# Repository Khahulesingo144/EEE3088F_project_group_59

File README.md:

# EEE3088F 2025 Micro-Mouse Power Subsystem

## Overview
This repository contains all design files and documentation for the power subsystem of the Micro-Mouse project, as part of the EEE3088F 2025 course at the University of Cape Town. 

The power module is responsible for delivering regulated power to the entire micro-mouse system, supporting motor driving, USB-C power input, battery monitoring and charging, and high-side switching for external loads.

## Project Objectives
- Design and manufacture a power PCB that:
  - Powers 4 motors (2x 200mA and 2x 500mA brushed DC)
  - Charges a LiPo battery from a 9V USB-C input (with 200mA and ~600mA charge modes)
  - Integrates an INA219 sensor for battery voltage/current monitoring
  - Supplies 5V @ 1.5A and 3.3V @ 300mA regulated outputs
  - Supports dual high-side external load switching (1A each)
  - Includes ON/OFF switching (<30μA off-state draw, 2A on-state peak)
- Stay within the strict $70 budget for manufacturing and components
- Ensure physical compatibility with the provided micro-mouse motherboard

## Tools Used
- **KiCad** – Schematic capture and PCB layout
- **JLCPCB** – PCB manufacturing and assembly
- **Git** – Version control
- **LaTeX** – Report writing

## Key Files
- `jlcpcb/production_files/GERBER-EEE3088F_2025_Project.zip` – Final Gerber files for PCB manufacturing
- `jlcpcb/production_files/BOM-EEE3088F_2025_Project.csv` – Bill of Materials for JLCPCB
- `jlcpcb/production_files/CPL-EEE3088F_2025_Project.csv` – Pick and Place file for assembly

## Contributors
- **Student 1**: Khahule Singo, Student Number: SNGKHA008
- **Student 2**: Otsile Diale, Student Number: DLXOTS001

Each student is responsible for distinct sections of the design and has submitted an individual report accordingly.

## License
This repository is intended for academic use only. Please do not reproduce or redistribute without permission.

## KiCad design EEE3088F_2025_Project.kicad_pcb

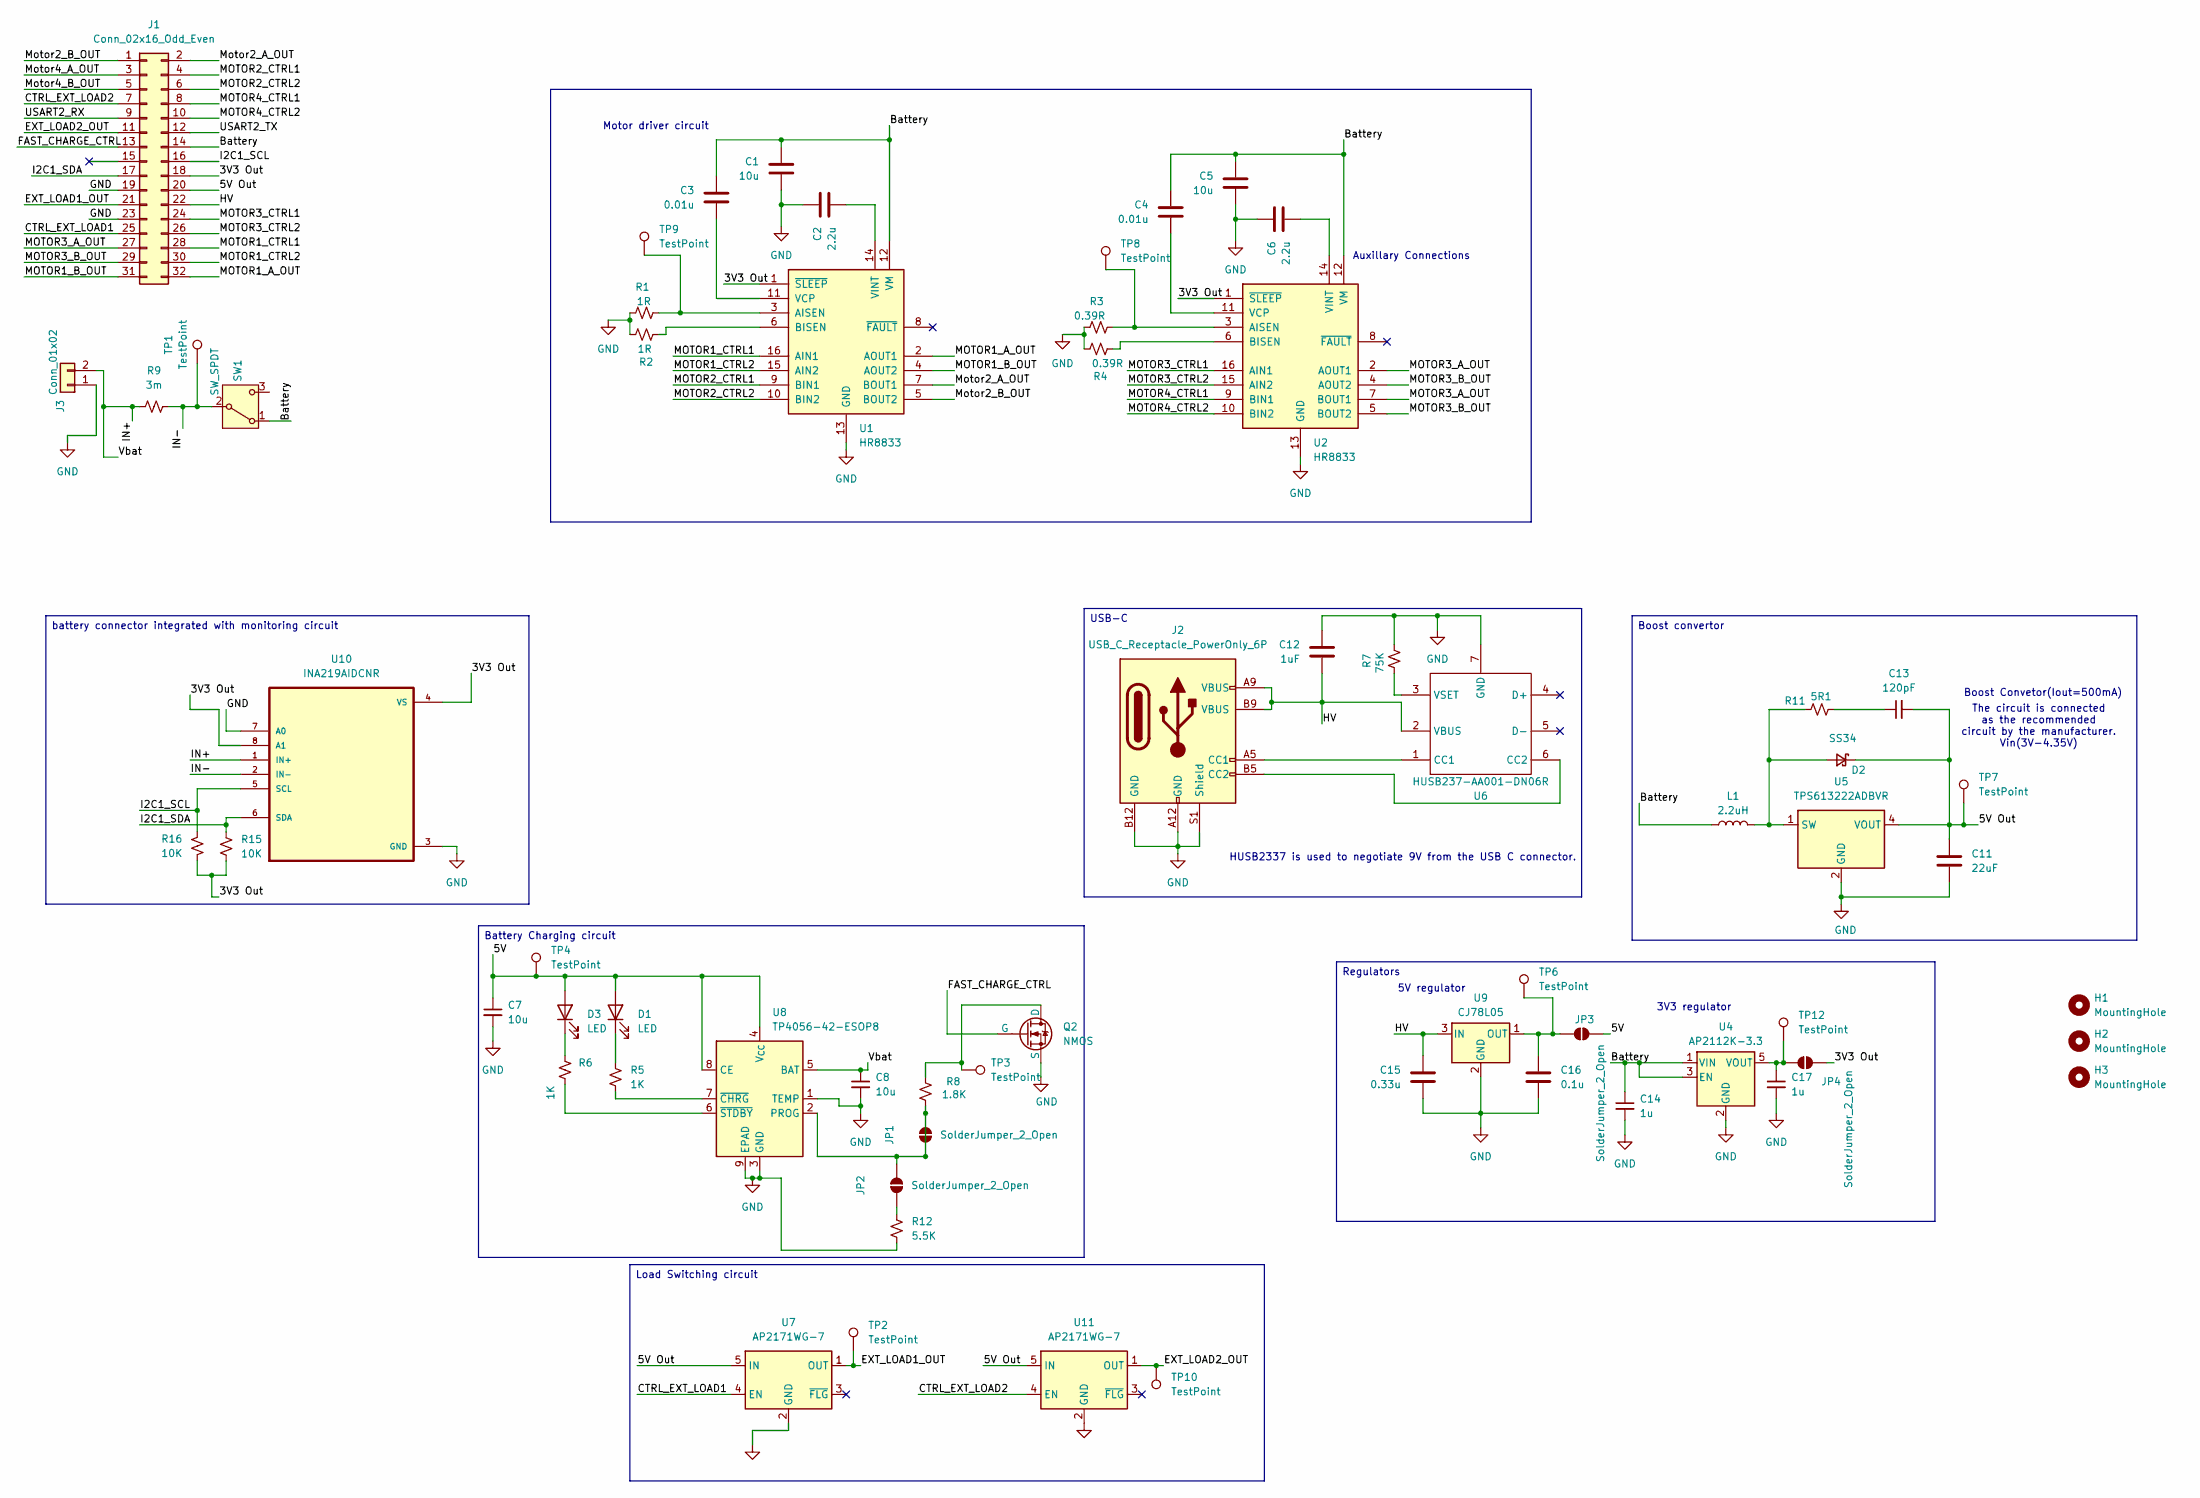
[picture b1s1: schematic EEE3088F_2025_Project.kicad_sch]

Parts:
C1, C5, C7, C8: 10u; C_0805_2012Metric_Pad1.18x1.45mm_HandSolder
C2, C6: 2.2u; C_0805_2012Metric_Pad1.18x1.45mm_HandSolder; LCSC C377773
C3, C4: 0.01u; C_0805_2012Metric_Pad1.18x1.45mm_HandSolder; LCSC C1710
C11: 22uF; C_0805_2012Metric_Pad1.18x1.45mm_HandSolder
C12: 1uF; C_0805_2012Metric_Pad1.18x1.45mm_HandSolder
C13: 120pF; C_0805_2012Metric_Pad1.18x1.45mm_HandSolder; LCSC C18438
C14: 1u; C_0805_2012Metric_Pad1.18x1.45mm_HandSolder
C15: 0.33u; C_0201_0603Metric_Pad0.64x0.40mm_HandSolder; LCSC C5139492
C16: 0.1u; C_0201_0603Metric_Pad0.64x0.40mm_HandSolder; LCSC C1525
C17: 1u; C_0805_2012Metric_Pad1.18x1.45mm_HandSolder; LCSC C28323
D1, D3: LED; LED_0201_0603Metric_Pad0.64x0.40mm_HandSolder
D2: SS34; D_SMA; LCSC C8678
H1, H2, H3: MountingHole; MountingHole_3.2mm_M3_DIN965_Pad
J1: Conn_02x16_Odd_Even; PinHeader_2x16_P2.54mm_Vertical
J2: USB_C_Receptacle_PowerOnly_6P; USB_C_Receptacle_GCT_USB4125-xx-x_6P_TopMnt_Horizontal; LCSC C456012
J3: Conn_01x02; JST_PH_S2B-PH-K_1x02_P2.00mm_Horizontal; LCSC C541760
JP1, JP2, JP3, JP4: SolderJumper_2_Open; SolderJumper-2_P1.3mm_Open_Pad1.0x1.5mm
L1: 2.2uH; L_1008_2520Metric_Pad1.43x2.20mm_HandSolder; LCSC C86092
Q2: NMOS; SOT-23-3; LCSC C20917
R1, R2: 1R; R1206; LCSC C17928
R3, R4: 0.39R; R1206; LCSC C188072
R5, R6: 1K; R_0201_0603Metric_Pad0.64x0.40mm_HandSolder
R7: 75K; R_0603_1608Metric_Pad0.98x0.95mm_HandSolder; LCSC C23242
R8: 1.8K; R_0201_0603Metric_Pad0.64x0.40mm_HandSolder; LCSC C4177
R9: 3m; R2512; LCSC C5375459
R11: 5R1; R_0805_2012Metric_Pad1.20x1.40mm_HandSolder; LCSC C17724
R12: 5.5K; R_0201_0603Metric_Pad0.64x0.40mm_HandSolder; LCSC C4382
R15, R16: 10K; R1206
SW1: SW_SPDT; SW_Slide_SPDT_Angled_CK_OS102011MA1Q; LCSC C431548
TP1, TP2, TP3, TP4, TP6, TP7, TP8, TP9, TP10, TP12: TestPoint; TestPoint_THTPad_D2.0mm_Drill1.0mm
U1, U2: HR8833; TSSOP-16_4.4x5mm_P0.65mm; LCSC C128666
U4: AP2112K-3.3; SOT-25-5_L2.9-W1.6-P0.95-LS2.8-BL; LCSC C51118
U5: TPS613222ADBVR; SOT-23-5; LCSC C2071163
U6: HUSB237-AA001-DN06R; DFN-6-1EP_2x2mm_P0.65mm_EP1.01x1.7mm; LCSC C22373734
U7, U11: AP2171WG-7; SOT-25-5_L2.9-W1.6-P0.95-LS2.8-BL; LCSC C110466
U8: TP4056-42-ESOP8; SOIC-8-1EP_3.9x4.9mm_P1.27mm_EP2.41x3.3mm_ThermalVias; LCSC C16581
U9: CJ78L05; SOT-89-3; LCSC C2079
U10: INA219AIDCNR; SOT-23-8_Handsoldering; LCSC C87469

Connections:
/3V3 Out: J1.18, JP4.1 (A), R15.2, R16.2, U1.1 (~SLEEP), U2.1 (~SLEEP), U10.4 (VS), U10.8 (A1)
/5V: C7.1, D1.2 (A), D3.2 (A), JP3.1 (A), TP4.1, U8.4 (V_{CC}), U8.8 (CE)
/5V Out: C11.1, C13.2, D2.1 (K), J1.20, TP7.1, U5.4 (VOUT), U7.5 (IN), U11.5 (IN)
/Battery: C1.1, C3.1, C4.1, C5.1, C14.1, J1.14, L1.1, SW1.1 (A), U1.12 (VM), U2.12 (VM), U4.1 (VIN), U4.3 (EN)
/CTRL_EXT_LOAD1: J1.25, U7.4 (EN)
/CTRL_EXT_LOAD2: J1.7, U11.4 (EN)
/EXT_LOAD1_OUT: J1.21, TP2.1, U7.1 (OUT)
/EXT_LOAD2_OUT: J1.11, TP10.1, U11.1 (OUT)
/FAST_CHARGE_CTRL: J1.13, Q2.2 (G)
/HV: C12.2, C15.1, J1.22, J2.A9 (VBUS), J2.B9 (VBUS), U6.2 (VBUS), U9.3 (IN)
/I2C1_SCL: J1.16, R16.1, U10.5 (SCL)
/I2C1_SDA: J1.17, R15.1, U10.6 (SDA)
/IN+: C8.1, J3.2, R9.1, U8.5 (BAT), U10.1 (IN+)
/IN-: R9.2, SW1.2 (B), TP1.1, U10.2 (IN-)
/MOTOR1_A_OUT: J1.32, U1.2 (AOUT1)
/MOTOR1_B_OUT: J1.31, U1.4 (AOUT2)
/MOTOR1_CTRL1: J1.28, U1.16 (AIN1)
/MOTOR1_CTRL2: J1.30, U1.15 (AIN2)
/MOTOR2_CTRL1: J1.4, U1.9 (BIN1)
/MOTOR2_CTRL2: J1.6, U1.10 (BIN2)
/MOTOR3_A_OUT: J1.27, U2.2 (AOUT1), U2.7 (BOUT1)
/MOTOR3_B_OUT: J1.29, U2.4 (AOUT2), U2.5 (BOUT2)
/MOTOR3_CTRL1: J1.24, U2.16 (AIN1)
/MOTOR3_CTRL2: J1.26, U2.15 (AIN2)
/MOTOR4_CTRL1: J1.8, U2.9 (BIN1)
/MOTOR4_CTRL2: J1.10, U2.10 (BIN2)
/Motor2_A_OUT: J1.2, U1.7 (BOUT1)
/Motor2_B_OUT: J1.1, U1.5 (BOUT2)
/Motor4_A_OUT: J1.3
/Motor4_B_OUT: J1.5
/USART2_RX: J1.9
/USART2_TX: J1.12
GND: C1.2, C2.1, C5.2, C6.1, C7.2, C8.2, C11.2, C12.1, C14.2, C15.2, C16.2, C17.2, H1.1, H2.1, H3.1, J1.19, J1.23, J2.A12 (GND), J2.B12 (GND), J2.S1 (Shield), J3.1, Q2.3 (S), R1.1, R2.1, R3.1, R4.1, R7.1, R12.2, U1.13 (GND), U2.13 (GND), U4.2 (GND), U5.2 (GND), U6.7 (GND), U7.2 (GND), U8.1 (TEMP), U8.3 (GND), U8.9 (EPAD), U9.2 (GND), U10.3 (GND), U10.7 (A0), U11.2 (GND)
unnamed: C13.1, R11.2
unnamed: D1.1 (K), R5.1
unnamed: D2.2 (A), L1.2, R11.1, U5.1 (SW)
unnamed: D3.1 (K), R6.1
unnamed: J2.A5 (CC1), U6.1 (CC1)
unnamed: J2.B5 (CC2), U6.6 (CC2)
unnamed: JP1.1 (A), JP1.2 (B), JP2.2 (B), R8.2, U8.2 (PROG)
unnamed: JP2.1 (A), R12.1
unnamed: C16.1, JP3.2 (B), TP6.1, U9.1 (OUT)
unnamed: C17.1, JP4.2 (B), TP12.1, U4.5 (VOUT)
unnamed: Q2.1 (D), R8.1, TP3.1
unnamed: R1.2, TP9.1, U1.3 (AISEN)
unnamed: R2.2, U1.6 (BISEN)
unnamed: C3.2, U1.11 (VCP)
unnamed: C2.2, U1.14 (VINT)
unnamed: R3.2, TP8.1, U2.3 (AISEN)
unnamed: R4.2, U2.6 (BISEN)
unnamed: C4.2, U2.11 (VCP)
unnamed: C6.2, U2.14 (VINT)
unnamed: R7.2, U6.3 (VSET)
unnamed: R5.2, U8.7 (~CHRG)
unnamed: R6.2, U8.6 (~STDBY)

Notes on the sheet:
HUSB2337 is used to negotiate 9V from the USB C connector.
5V regulator
Auxillary Connections
Boost Convetor(Iout=500mA)
3V3 regulator
The circuit is connected as the recommended circuit by the manufacturer. Vin(3V-4.35V)
Motor driver circuit
Load Switching circuit
Battery Charging circuit
USB-C
battery connector integrated with monitoring circuit
Regulators
Boost convertor

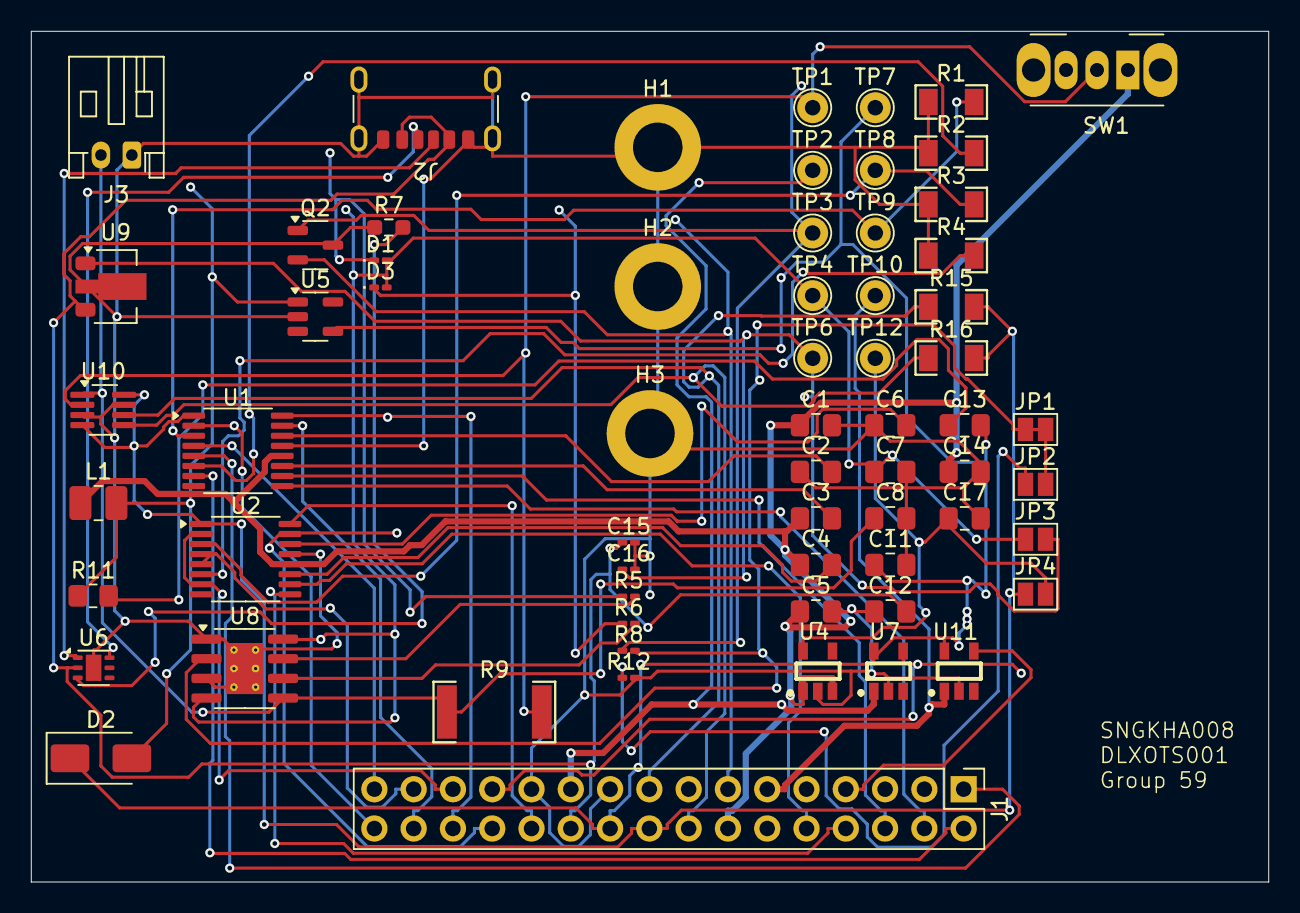
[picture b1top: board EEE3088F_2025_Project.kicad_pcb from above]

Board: 2 copper layers, 80.0 x 55.0 mm, 64 parts (0 on the bottom side), 51 nets.

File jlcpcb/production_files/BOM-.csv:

Comment,Designator,Footprint,LCSC,Quantity
HR8833,"U1,U2",TSSOP-16_4.4x5mm_P0.65mm,C128666,2
HT7533-1,"U4,U9",SOT-89-3,C14289,2
MIC2026-1YM,U3,SOIC-8_3.9x4.9mm_P1.27mm,C144190,1
10u,"C1,C10,C15,C16,C5,C7,C8,C9",C_0805_2012Metric_Pad1.18x1.45mm_HandSolder,C15850,8
TP4056-42-ESOP8,U8,SOIC-8-1EP_3.9x4.9mm_P1.27mm_EP2.41x3.3mm_ThermalVias,C16581,1
0.01u,"C3,C4",C_0805_2012Metric_Pad1.18x1.45mm_HandSolder,C1710,2
1.6K,R8,R_0201_0603Metric_Pad0.64x0.40mm_HandSolder,C17394,1
5R1,R11,R_0805_2012Metric_Pad1.20x1.40mm_HandSolder,C17724,1
10K,"R15,R16",R_1206_3216Metric_Pad1.30x1.75mm_HandSolder,C17902,2
1R,"R1,R2",R_1206_3216Metric_Pad1.30x1.75mm_HandSolder,C17928,2
120pF,C13,C_0805_2012Metric_Pad1.18x1.45mm_HandSolder,C18438,1
0.36R,"R3,R4",R_1206_3216Metric_Pad1.30x1.75mm_HandSolder,C188072,2
TPS613222ADBV,U5,SOT-23-5,C2071163,1
NMOS,Q2,Infineon_PG-HSOF-8-1,C20917,1
1K,"R5,R6",R_0201_0603Metric_Pad0.64x0.40mm_HandSolder,C21190,2
HUSB237-AA001-DN06R,U6,DFN-6-1EP_2x2mm_P0.65mm_EP1.01x1.7mm,C22373734,1
15K,R12,R_0201_0603Metric_Pad0.64x0.40mm_HandSolder,C22809,1
LED,D1,LED_0201_0603Metric_Pad0.64x0.40mm_HandSolder,C2286,1
LED,D3,LED_0201_0603Metric_Pad0.64x0.40mm_HandSolder,C2290,1
75K,R7,R_0603_1608Metric_Pad0.98x0.95mm_HandSolder,C23242,1
1uF,C12,C_0805_2012Metric_Pad1.18x1.45mm_HandSolder,C28323,1
2.2u,"C2,C6",C_0805_2012Metric_Pad1.18x1.45mm_HandSolder,C377773,2
SW_SPDT,SW1,SW_Slide_SPDT_Angled_CK_OS102011MA1Q,C431541,1
USB_C_Receptacle_PowerOnly_6P,J2,USB_C_Receptacle_GCT_USB4125-xx-x_6P_TopMnt_Horizontal,C456012,1
22uF,C11,C_0805_2012Metric_Pad1.18x1.45mm_HandSolder,C45783,1
3m,R14,R_Shunt_Vishay_WSK2512_6332Metric_T2.21mm,C5375459,1
2.2uH,L1,L_1008_2520Metric_Pad1.43x2.20mm_HandSolder,C86092,1
SS34,D2,D_SMA,C8678,1
INA219AIDCNR,U10,SOT-23-8_Handsoldering,C87469,1

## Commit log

2025-03-20 Add files via upload
    Created a file to be edited to create the project schematic
2025-03-20 Delete EEE3088F_2025_Project.zip
    Zip file deleted
2025-03-20 Add files via upload
    Added Kicad schematic file to be used for the project
2025-03-20 added dummy component to test commit
2025-03-20 added other file and backups
2025-03-20 Update README.md
    Added purpose of the repository
2025-03-21 Addded motor drivers and connector
2025-03-22 Added dummy charging IC, struggling to add JLCPCB to Kicad
2025-03-22 made minor changes to labels
2025-03-22 Added INA219
2025-03-22 Added a switch, 3V3 and 5V out, intergrated USB C
2025-03-24 added footprint for usb c connector
2025-03-24 Added INA219, status LEDs for charging
2025-03-24 Change charging IC to have 5 pins
2025-03-25 Adjusted the boost conv to get 500mA
2025-03-25 Added footprints and LCSC numbers
2025-03-26 Added lcsc number for resistors and capacitors
2025-03-26 Changed charging IC
2025-03-26 Added new footprint for 1*2 connector
2025-03-26 Changed the configuration for INA219
2025-03-26 Added LCSC numbers and changed switch to SPDT
2025-03-26 fixed footprint for SW1 to be vertical pin
2025-03-27 Changed regulator and NMOS footprint
2025-03-27 Added edge cuts
2025-03-27 Added testpoints and board layout shape
2025-03-27 Added B.Cu layer as ground plane
2025-03-27 Added mounting holes
2025-03-28 Added mounting holes and solder jumpers
2025-03-28 added routing
2025-03-29 Final files used for submission
2025-04-12 Update README.md
    Updated Readme
